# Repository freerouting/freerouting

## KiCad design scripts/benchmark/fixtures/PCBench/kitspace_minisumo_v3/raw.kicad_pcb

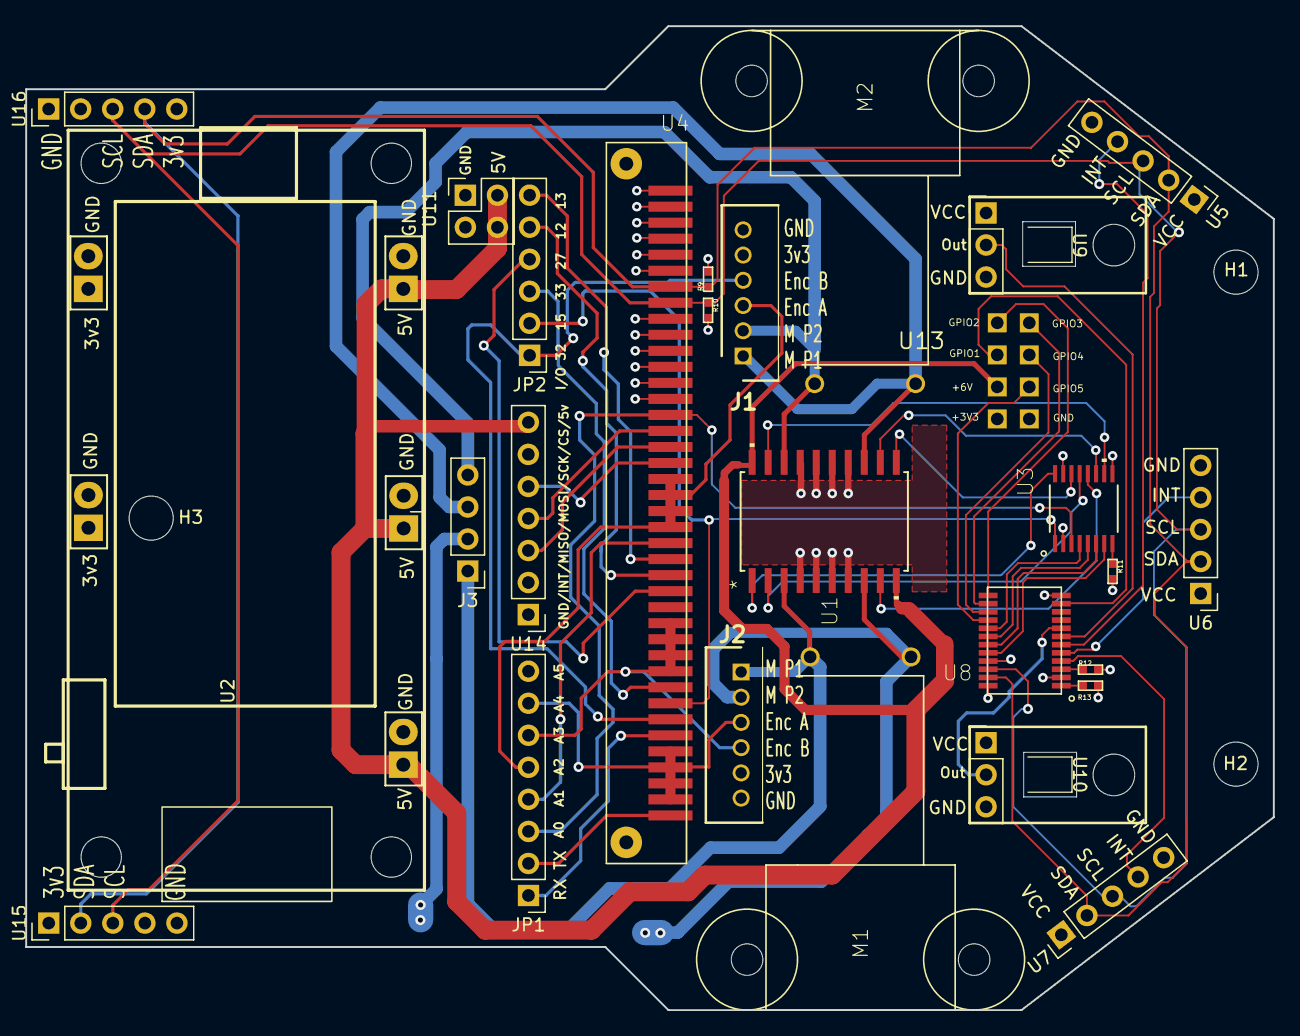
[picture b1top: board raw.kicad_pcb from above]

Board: 4 copper layers, 98.9 x 78.0 mm, 30 parts (0 on the bottom side), 48 nets.

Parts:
H1, H2, H3: MountingHole; MountingHole_3.5mm
J1: Right Motor; SHDR6W50P0X200_1X6_1390X450X600P
J2: Left Motor; SHDR6W50P0X200_1X6_1390X450X600P
J3: Motor Connector2; PinHeader_1x04_P2.54mm_Vertical
JP1: Conn_01x08; PinHeader_1x08_P2.54mm_Vertical
JP2: Conn_01x06; PinHeader_1x06_P2.54mm_Vertical
M1, M2: N20_MOTOR; N20-MOTOR-BRACKET
R9, R10, R11, R12, R13: 10k; RES_0402
U1: L293DD; SO-20
U2: 16340_Battery_Module; 16340 Battery Module
U3: TXB0106PWRPW16-L; PW16-L
U4: BBC Micro:bit; CYCLONE_MICROBIT_VERTICAL
U5: VL53L1X Right; PinHeader_1x05_P2.54mm_Vertical
U6: VL53L1X Center; PinHeader_1x05_P2.54mm_Vertical
U7: VL53L1X Left; PinHeader_1x05_P2.54mm_Vertical
U8: TCA9539PWR; 24-TSSOP
U9: NW; SparkFun QRE1113
U10: NE; SparkFun QRE1113
U11: Conn_02x02_Top_Bottom; PinHeader_2x02_P2.54mm_Vertical
U13: SUMO_IO
U14: Conn_01x07; PinHeader_1x07_P2.54mm_Vertical
U15, U16: Conn_01x05_2; PinHeader_1x05_P2.54mm_Vertical

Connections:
+3V3: J1.5, J2.5, R9.P$2, R10.P$2, R11.P$2, R12.P$2, R13.P$2, U2.3 (3v3), U3.2 (VCCA), U4.3.3V@9 (+3.3V), U4.3.3V@10 (+3.3V), U4.3.3V@11 (+3.3V), U4.3.3V@12 (+3.3V), U4.3.3V@13 (+3.3V), U4.3.3V@14 (+3.3V), U5.1, U6.1, U7.1, U8.24 (VCC), U9.+3V3, U10.+3V3, U13.3V3 (+3V3), U15.1, U16.5
+5V: U1.10 (VS_SUPPLY), U1.20 (VSS_LOGIC), U2.1 (5V), U3.15 (VCCB), U11.2, U11.4, U13.6V (+6V), U14.7
/INPUT_1: U3.4 (A3), U8.17 (P14)
/INPUT_2: U3.5 (A4), U8.18 (P15)
/INPUT_3: U3.6 (A5), U8.19 (P16)
/INPUT_4: U3.7 (A6), U8.20 (P17)
/IO1: U8.11 (P07), U13.GPIO1
/IO2: U8.13 (P10), U13.GPIO2
/IO3: U8.14 (P11), U13.GPIO3
/IO4: U8.15 (P12), U13.GPIO4
/IO5: U8.16 (P13), U13.GPIO5
/ML1: J2.1, J3.1, M1.1, U1.3 (OUTPUT_1)
/ML2: J2.2, J3.2, M1.2, U1.8 (OUTPUT_2)
/MR1: J1.1, J3.3, M2.1, U1.13 (OUTPUT_3)
/MR2: J1.2, J3.4, M2.2, U1.18 (OUTPUT_4)
/NE: U8.8 (P04), U10.SIGNAL
/NW: U8.7 (P03), U9.SIGNAL
/XS1: U7.4, U8.4 (P00)
/XS2: U6.4, U8.5 (P01)
/XS3: U5.4, U8.6 (P02)
A0: JP1.3, U3.3 (A2), U4.P16
A1: JP1.4, U4.RESERVED (P12(Res))
A2: J1.3, JP1.5, U4.P2_ANALOG_IN@19 (P2_ANALOG_IN), U4.P2_ANALOG_IN@20 (P2_ANALOG_IN), U4.P2_ANALOG_IN@21 (P2_ANALOG_IN), U4.P2_ANALOG_IN@22 (P2_ANALOG_IN)
A3: J2.4, JP1.6, U4.P1_ANALOG_IN@28 (P1_ANALOG_IN), U4.P1_ANALOG_IN@29 (P1_ANALOG_IN), U4.P1_ANALOG_IN@30 (P1_ANALOG_IN), U4.P1_ANALOG_IN@31 (P1_ANALOG_IN)
A4: J2.3, JP1.7, U4.P0_ANALOG_IN@36 (P0_ANALOG_IN), U4.P0_ANALOG_IN@37 (P0_ANALOG_IN), U4.P0_ANALOG_IN@38 (P0_ANALOG_IN), U4.P0_ANALOG_IN@39 (P0_ANALOG_IN)
GND: J1.6, J2.6, U1.4 (GND_2), U1.5 (GND_3), U1.6 (GND_4), U1.7 (GND_5), U1.14 (GND_6), U1.15 (GND_7), U1.16 (GND_8), U1.17 (GND), U2.2 (GND), U2.4 (GND), U3.9 (GND), U4.GND@1 (GND), U4.GND@2 (GND), U4.GND@3 (GND), U4.GND@4 (GND), U4.GND@5 (GND), U4.GND@6 (GND), U5.5, U6.5, U7.5, U8.2 (A1), U8.12 (GND), U8.21 (A0), U9.GND, U10.GND, U11.1, U11.3, U13.GND, U14.1, U15.5, U16.1
IO12: JP2.5, U4.P10_LED_COL_3_ANALO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 (P10_LED_COL_3_ANAOLOG_IN)
IO13: JP2.6, U4.P11_BUTTON_B
IO15: JP2.2, U3.1 (A1), U4.P6_LED_COL_9
IO16: JP1.1, U4.P4_LED_COL_2_ANALOG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
IO17: JP1.2, U4.P3_LED_COL_1_ANALOG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
IO27: JP2.4, U4.P9_LED_COL_7
IO32: J1.4, JP2.1, U4.P5_BUTTON_A
IO33: JP2.3, U4.P7_LED_COL8 (P7_LED_COL_8)
MISO: U4.P14_MISO, U14.3
MOSI: U4.P15_MOSI, U14.4
unnamed: R11.P$1, U3.8 (OE)
unnamed: R12.P$1, U8.3 (~RESET)
unnamed: R13.P$1, U8.1 (~INT)
unnamed: U1.1 (ENABLE_1), U3.16 (B1)
unnamed: U1.2 (INPUT_1), U3.13 (B3)
unnamed: U1.9 (INPUT_2), U3.12 (B4)
unnamed: U1.11 (ENABLE_2), U3.14 (B2)
unnamed: U1.12 (INPUT_3), U3.11 (B5)
unnamed: U1.19 (INPUT_4), U3.10 (B6)
SCK: U4.P13_SCK, U14.5
SCL: R10.P$1, U4.P21_SCL (P19_SCL), U5.3, U6.3, U7.3, U8.22 (SCL), U15.3, U16.3
SDA: R9.P$1, U4.P20_SDA, U5.2, U6.2, U7.2, U8.23 (SDA), U15.2, U16.4

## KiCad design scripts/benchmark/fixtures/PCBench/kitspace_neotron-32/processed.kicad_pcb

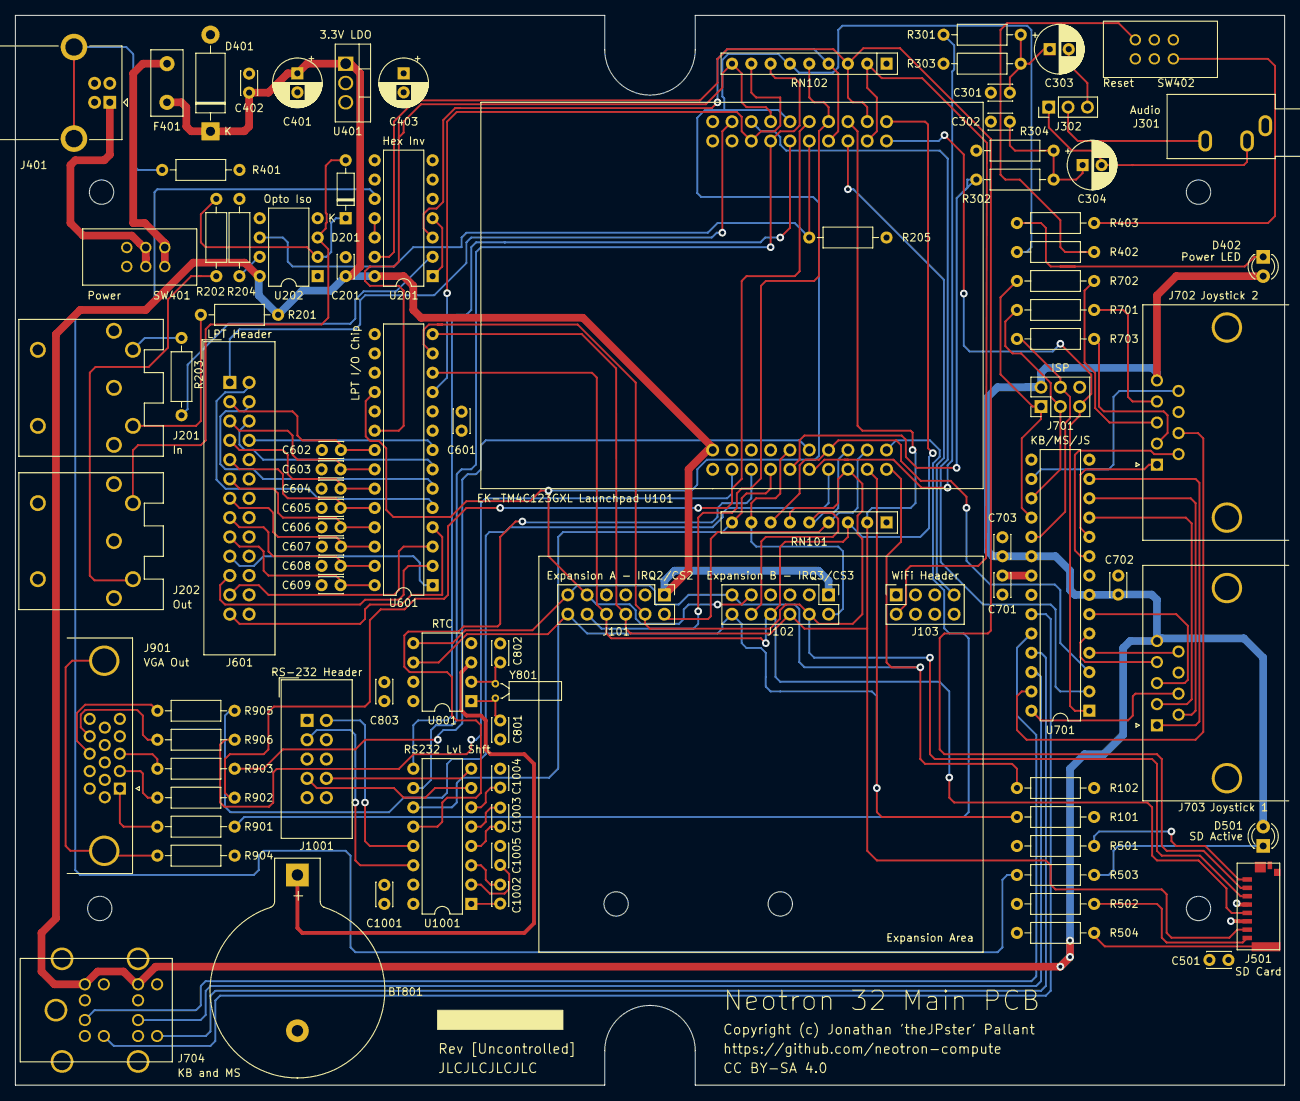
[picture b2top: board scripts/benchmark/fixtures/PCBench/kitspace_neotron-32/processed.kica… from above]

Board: 4 copper layers, 166.9 x 140.7 mm, 97 parts (0 on the bottom side), 117 nets.

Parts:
BT801: CR2032; BatteryHolder_Keystone_103_1x20mm
C201, C402, C501, C601, C701, C702, C703, C803, C1001, C1002, C1003, C1004, C1005: 100n; C_Disc_D3.0mm_W2.0mm_P2.50mm
C301, C302: 33n; C_Disc_D3.0mm_W2.0mm_P2.50mm
C303, C304, C401: 10u; CP_Radial_D6.3mm_P2.50mm
C403: 47u; CP_Radial_D6.3mm_P2.50mm
C602, C603, C604, C605, C606, C607, C608, C609: 22n; C_Disc_D3.0mm_W2.0mm_P2.50mm
C801, C802: 6p; C_Disc_D3.0mm_W2.0mm_P2.50mm
D201: 1N4148; D_DO-35_SOD27_P7.62mm_Horizontal
D401: SA5.0A; D_DO-15_P12.70mm_Horizontal
D402, D501: Red LED; LED_D3.0mm
F401: 250mA PTC; Fuse_Littelfuse_395Series
H101, H102, H103, H104, H105, H106: MountingHole; MountingHole_3.2mm_M3
J101, J102: Conn_02x06; PinHeader_2x06_P2.54mm_Vertical
J103: Conn_02x04; PinSocket_2x04_P2.54mm_Vertical
J201, J202: DIN-5 180 degree; 5P180_DIN_Socket
J301: 3.5mm Audio Jack TRS; Jack_3.5mm_CUI_SJ1-3533NG_Horizontal
J302: Conn_01x03_Male; PinHeader_1x03_P2.54mm_Vertical
J401: USB_B; USB_B_OST_USB-B1HSxx_Horizontal
J501: micro SD Card; Molex_4730_2651
J601: Conn_02x13_Header; IDC-Header_2x13_P2.54mm_Vertical
J701: AVR-ISP-6; PinHeader_2x03_P2.54mm_Vertical
J702, J703: DE9 Male; DSUB-9_Male_Horizontal_P2.77x2.84mm_EdgePinOffset14.56mm_Ho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
J704: Double-mini-DIN-6; Double_mini-DIN_6
J901: DB15HD_Female; DSUB-15-HD_Female_Horizontal_P2.29x1.98mm_EdgePinOffset3.03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
J1001: Conn_02x05; IDC-Header_2x05_P2.54mm_Vertical
R101, R102, R701, R702, R703: 1k; R_Axial_DIN0207_L6.3mm_D2.5mm_P10.16mm_Horizontal
R201, R202, R203: 220; R_Axial_DIN0207_L6.3mm_D2.5mm_P10.16mm_Horizontal
R204: 10k; R_Axial_DIN0207_L6.3mm_D2.5mm_P10.16mm_Horizontal
R205: 470; R_Axial_DIN0207_L6.3mm_D2.5mm_P10.16mm_Horizontal
R301, R302: 270; R_Axial_DIN0207_L6.3mm_D2.5mm_P10.16mm_Horizontal
R303, R304: 150; R_Axial_DIN0207_L6.3mm_D2.5mm_P10.16mm_Horizontal
R401, R504, R904: DNF; R_Axial_DIN0207_L6.3mm_D2.5mm_P10.16mm_Horizontal
R402, R403, R503, R901, R902, R903, R905, R906: 330; R_Axial_DIN0207_L6.3mm_D2.5mm_P10.16mm_Horizontal
R501, R502: 47k; R_Axial_DIN0207_L6.3mm_D2.5mm_P10.16mm_Horizontal
RN101, RN102: 47k x 8; R_Array_SIP9
SW401: SW_Push_DPDT_ON_OFF; PHB2UEETS1A
SW402: SW_Push_DPDT_ON_MO; PHB2UEETS1A
U101: EK-TM4C123GXL; Launchpad_4x10
U201: 74LS14; DIP-14_W7.62mm
U202: 6N138; DIP-8_W7.62mm
U401: TC1262-33; TO-220-3_Vertical
U601: MCP23S17_SP; DIP-28_W7.62mm
U701: ATmega328-PU; DIP-28_W7.62mm
U801: MCP7940N-xP; DIP-8_W7.62mm
U1001: ICL3232CPZMAX; DIP-16_W7.62mm
Y801: 32,768 Hz; Crystal_C26-LF_D2.1mm_L6.5mm_Horizontal

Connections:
+3V3: C403.1, C501.1, C601.1, C803.1, C1001.2, C1005.1, J101.3, J102.3, J103.1, J501.4, R101.2, R102.2, R205.2, R501.2, R502.2, U401.3, U601.9, U801.8, U1001.16
+5V: C201.1, C401.1, C402.1, C702.1, C703.1, D401.1, D402.2, D501.2, F401.1, J101.1, J102.1, J701.2, J702.5, J703.5, J704.4, J704.10, R201.2, U101.3.1, U201.14, U202.8, U401.1, U701.7, U701.20
+BATT: BT801.1, U801.3
/Audio/LEFT_CHAN: C304.2, J301.T, J302.1
/Audio/RIGHT_CHAN: C303.2, J302.3
/Audio/RIGHT_SPKR: J301.R, J302.2
/Keyboard, Mouse and Joystick/AT_MISO: J701.1, R702.2, U701.18
/Keyboard, Mouse and Joystick/AT_MOSI: J701.4, R703.2, U701.19
/Keyboard, Mouse and Joystick/AT_SCK: J701.3, R701.2, U701.17
/Keyboard, Mouse and Joystick/A_B_JS1: J703.6, U701.12
/Keyboard, Mouse and Joystick/A_B_JS2: J702.6, U701.9
/Keyboard, Mouse and Joystick/DOWN_JS1: J703.2, U701.11
/Keyboard, Mouse and Joystick/DOWN_JS2: J702.2, R703.1
/Keyboard, Mouse and Joystick/KB_CLK: J704.5, U701.23
/Keyboard, Mouse and Joystick/KB_DAT: J704.1, U701.24
/Keyboard, Mouse and Joystick/LEFT_GND_JS1: J703.3, U701.6
/Keyboard, Mouse and Joystick/LEFT_GND_JS2: J702.3, R702.1
/Keyboard, Mouse and Joystick/MS_CLK: J704.11, U701.25
/Keyboard, Mouse and Joystick/MS_DAT: J704.7, U701.26
/Keyboard, Mouse and Joystick/RIGHT_GND_JS1: J703.4, U701.5
/Keyboard, Mouse and Joystick/RIGHT_GND_JS2: J702.4, R701.1
/Keyboard, Mouse and Joystick/SELECT_JS1: J703.7, U701.28
/Keyboard, Mouse and Joystick/SELECT_JS2: J702.7, U701.27
/Keyboard, Mouse and Joystick/START_C_JS1: J703.9, U701.4
/Keyboard, Mouse and Joystick/START_C_JS2: J702.9, U701.16
/Keyboard, Mouse and Joystick/UP_JS1: J703.1, U701.13
/Keyboard, Mouse and Joystick/UP_JS2: J702.1, U701.10
/PA2_SPI_CLK: J101.8, J102.8, J501.5, RN101.3, U101.2.1, U601.12
/PA4_SPI_MISO: J101.6, J102.6, J501.7, RN101.2, U101.2.8, U601.14
/PA5_SPI_MOSI: J101.4, J102.4, J501.3, RN101.6, U101.1.8, U601.13
/PA6_I2C_SCL: J101.12, J102.12, R101.1, U101.1.9, U801.6
/PA7_I2C_SDA: J101.11, J102.11, R102.1, U101.1.1, U801.5
/PB0_U1RX: U101.1.3, U1001.12
/PB1_U1TX: RN101.9, U101.1.4, U1001.11
/PB4_VGA_HSYNC: R905.1, U101.1.7
/PB5_VGA_VSYNC: R906.1, U101.1.2
/PB7_VGA_GREEN: R902.2, U101.2.6
/PC4_U1RTS: RN102.7, U101.4.4, U1001.10
/PC5_U1CTS: U101.4.5, U1001.9
/PC6_MIDI_IN: R205.1, U101.4.6, U202.6
/PC7_MIDI_OUT: RN102.4, U101.4.7, U201.3
/PD3_VGA_BLUE: R903.2, U101.3.6
/PD6_U2RX: J103.7, U101.4.8
/PD7_U2TX: J103.2, RN102.2, U101.4.9
/PE0_U7RX: U101.2.3, U701.2
/PE1_U7TX: RN101.7, U101.3.7, U701.3
/PE4_AUDIO_L: R302.2, U101.1.5
/PE5_AUDIO_R: R301.2, U101.1.6
/PF1_VGA_RED: R901.2, U101.3.1
/Parallel Printer/ACK: J601.19, U601.1
/Parallel Printer/D0: C602.2, J601.3, U601.21
/Parallel Printer/D1: C603.2, J601.5, U601.22
/Parallel Printer/D2: C604.2, J601.7, U601.23
/Parallel Printer/D3: C605.2, J601.9, U601.24
/Parallel Printer/D4: C606.2, J601.11, U601.25
/Parallel Printer/D5: C607.2, J601.13, U601.26
/Parallel Printer/D6: C608.2, J601.15, U601.27
/Parallel Printer/D7: C609.2, J601.17, U601.28
/Parallel Printer/ERROR: J601.4, U601.6
/Parallel Printer/POUT: J601.23, U601.3
/Parallel Printer/RESET: J601.6, U601.7
/Parallel Printer/SELECT: J601.25, U601.4
/Parallel Printer/~BUSY: J601.21, U601.2
/Parallel Printer/~LF: J601.2, U601.5
/Parallel Printer/~SELPRI: J601.8, U601.8
/Power/UNFUSED_5V: F401.2, SW401.3, SW401.6
/Power/VUSB: J401.1, SW401.2, SW401.5
/RS-232 Serial Port/RS232_CTS_IN: J1001.8, U1001.8
/RS-232 Serial Port/RS232_RTS_OUT: J1001.7, U1001.7
/RS-232 Serial Port/RS232_RX_IN: J1001.2, U1001.13
/RS-232 Serial Port/RS232_TX_OUT: J1001.3, U1001.14
/~PA3_SPI_CS0: J501.2, RN102.3, U101.2.9, U201.13
/~PB2_STROBE: J601.1, U101.2.2
/~PB3_SPI_CS1: RN102.8, U101.4.3, U601.11
/~PB6_SPI_CS2: J101.10, RN102.5, U101.2.7
/~PD2_IRQ3: J102.2, RN101.8, U101.3.5
/~PE2_SPI_CS3: J102.10, RN101.5, U101.3.8
/~PE3_IRQ2: J101.2, RN101.4, U101.3.9
/~PF0_IRQ1: RN102.9, U101.2.4, U601.20
/~PF4_AT_RESET: J701.5, U101.4.1, U701.1
/~RESET: J101.9, J102.9, R402.1, RN102.6, U101.2.5, U601.18
GND: BT801.2, C201.2, C301.1, C302.1, C401.2, C402.2, C403.2, C501.2, C601.2, C602.1, C603.1, C604.1, C605.1, C606.1, C607.1, C608.1, C609.1, C701.1, C702.2, C703.2, C801.1, C802.2, C803.2, C1001.1, C1004.1, D401.2, J101.5, J101.7, J102.5, J102.7, J103.8, J201.2, J301.S, J401.4, J501.6, J601.10, J601.12, J601.14, J601.16, J601.18, J601.20, J601.22, J601.24, J601.26, J701.6, J702.8, J703.8, J704.3, J704.9, J901.5, J901.6, J901.7, J901.8, J1001.5, R204.1, R303.2, R304.2, R401.1, R504.2, R904.1, RN101.1, RN102.1, SW402.2, SW402.5, U101.2.1, U101.3.2, U201.5, U201.7, U201.9, U202.5, U401.2, U601.10, U601.15, U601.16, U601.17, U701.8, U701.22, U801.4, U1001.15
unnamed: C301.2, C303.1, R301.1, R303.1
unnamed: C302.2, C304.1, R302.1, R304.1
unnamed: C701.2, U701.21
unnamed: C801.2, U801.1, Y801.1
unnamed: C802.1, U801.2, Y801.2
unnamed: C1002.1, U1001.3
unnamed: C1002.2, U1001.1
unnamed: C1003.1, U1001.4
unnamed: C1003.2, U1001.5
unnamed: C1004.2, U1001.6
unnamed: C1005.2, U1001.2
unnamed: D201.1, R202.1, U202.2
unnamed: D201.2, J202.5, U202.3
unnamed: D402.1, R403.1
unnamed: D501.1, R503.1
unnamed: J201.4, R201.1
unnamed: J201.5, R203.2
unnamed: J202.4, R202.2
unnamed: J401.5, R401.2
unnamed: J501.1, R501.1
unnamed: J501.8, R502.1
unnamed: J501.9, R504.1
unnamed: J901.0, R904.2
unnamed: J901.1, R901.1
unnamed: J901.2, R902.1
unnamed: J901.3, R903.1
unnamed: J901.13, R905.2
unnamed: J901.14, R906.2
unnamed: R203.1, U201.2
unnamed: R204.2, U202.7
unnamed: R402.2, SW402.3
unnamed: R403.2, SW402.4
unnamed: R503.2, U201.10
unnamed: U201.1, U201.4
unnamed: U201.11, U201.12

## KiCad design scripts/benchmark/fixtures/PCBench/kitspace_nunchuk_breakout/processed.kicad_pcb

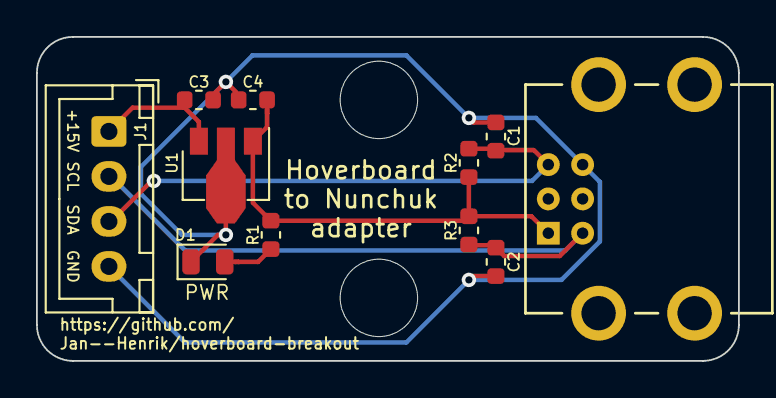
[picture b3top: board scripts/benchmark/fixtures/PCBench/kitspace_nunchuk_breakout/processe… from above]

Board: 2 copper layers, 39.0 x 18.0 mm, 13 parts (0 on the bottom side), 6 nets.

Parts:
C1, C2: 10p; C_0603_1608Metric
C3, C4: 1uF; C_0603_1608Metric
D1: LED; LED_0805_2012Metric
H1, H2: MountingHole; MountingHole_4.3mm_M4
J1: Conn_01x04; JST_XH_B04B-XH-A_1x04_P2.50mm_Vertical
P1: CONN_WII
R1: 220Ohm; R_0603_1608Metric
R2, R3: 3k3; R_0603_1608Metric
U1: L78L33_SOT89; SOT-89-3

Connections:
GND: C1.2, C2.1, C3.2, C4.2, D1.1, J1.4, P1.6, U1.2
unnamed: D1.2, R1.1
SCL: C2.2, J1.2, P1.2, R3.2
SDA: C1.1, J1.3, P1.5, R2.2
VCC: C4.1, P1.1, R1.2, R2.1, R3.1, U1.1
VDD: C3.1, J1.1, U1.3

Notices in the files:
scripts/benchmark/fixtures/PCBench/kitspace_minisumo_v3/raw.kicad_pcb:
CERN-OHl-P
scripts/benchmark/fixtures/PCBench/kitspace_neotron-32/processed.kicad_pcb:
Copyright (c) Jonathan 'theJPster' Pallant
CC BY-SA 4.0
